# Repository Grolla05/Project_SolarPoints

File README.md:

# 💡 Project Solar Points — Smart Lighting for Low-Infrastructure Areas

> Light where there’s no infrastructure. Safety through simplicity and efficiency.

---

## 🌙 O que é o Solar Points?

O **Solar Points** é um sistema de iluminação pública autônomo e inteligente pensado para locais com pouca ou nenhuma infraestrutura elétrica, como:

- Paradas de ônibus
- Vielas e ruas estreitas
- Praças públicas
- Regiões periféricas e isoladas
- Áreas externas de residências

O objetivo permanece o mesmo: aumentar a segurança e o bem-estar comunitário com uma solução de baixo custo, sustentável e de fácil manutenção.

---

## 🔁 Evolução do projeto: de totalmente analógico para arquitetura digital

Inicialmente o projeto foi concebido como **100% analógico** (apenas componentes discretos e circuitos analógicos). Com as necessidades de sensoriamento mais preciso, flexibilidade operacional e otimização de consumo, o projeto evoluiu para uma **arquitetura digital/híbrida** baseada em microcontrolador e periféricos.

Essa mudança preserva os princípios de simplicidade, robustez e baixo consumo, ao mesmo tempo que agrega capacidades importantes:

- **Leitura digital de sensores** (intensidade de luz, distância/presença)
- **Decisões e temporizações programáveis** via firmware leve
- **Gerenciamento inteligente de energia** (controle de conversores DC-DC, modos de sono)
- **Comunicação entre módulos** via I2C/GPIO quando necessário

> A imagem anexada ao repositório ilustra o bloco funcional do novo design: microcontrolador central, sensores de luz e distância, gerenciamento de energia, baterias e conversores DC-DC.

---

## ⚙️ Principais funcionalidades (atualizado)

- **Ativação automática** baseada em sensores de luminosidade e presença
- **Modos ajustáveis** via firmware (p.ex. sensibilidades, temporização)
- **Operação autônoma** com painéis solares e baterias
- **Gestão adequada de energia** com conversores DC-DC e técnicas de baixo consumo
- **Projeto modular e replicável** com possibilidade de atualização de firmware

---

## 🛠️ Tecnologias e componentes (atualizado)

- **Microcontrolador** (unidade central de controle) — responsável por leitura de sensores e lógica de acionamento
- **Sensor de luminosidade** (LDR/photodiode + ADC) — medida de intensidade luminosa
- **Sensor de distância/presença** (ultrassom/IR) — detectar passagem ou presença
- **Conversores DC-DC** (step-up/step-down) — fornecimento estável para LEDs e eletrônica
- **Gestão de energia / Power Management** (monitoramento de bateria, carregamento solar)
- **Bateria recarregável e painéis solares**
- **LEDs de potência** para iluminação pública
- **Interfaces**: GPIOs para sinalização/controle, I2C para sensores/power ICs quando aplicável

---

## 🔍 Diagrama funcional

O diagrama no repositório mostra os blocos principais interconectados:

- 1 — Baterias (alimentação)
- 4 — Power Management (monitoramento/carregador)
- 11 — Conversão DC-DC (alimentação dos LEDs e eletrônica)
- 2 — Microcontrolador (núcleo lógico)
- 5 — Medição de intensidade luminosa (sensor)
- 6 — Sensor de distância/presença
- 3 — LED de status / power

O microcontrolador realiza a lógica central: lê sensores (GPIOs/ADC/I2C), decide quando ligar os LEDs e controla os conversores para otimizar consumo.

---

## ✨ Aplicações no mundo real

O Solar Points continua ideal para iluminar pontos sem infraestrutura elétrica: pontos de ônibus, caminhos em áreas rurais, entradas de condomínios e outras localidades onde uma solução autônoma e resiliente faz diferença.

---

## 👥 Autores

Desenvolvido por:

- **Felipe Grolla Freitas** – Engenharia de Controle e Automação (PUC-Campinas)
- **Guilherme Oliveira Nogueira** – Engenharia de Controle e Automação (PUC-Campinas)
- **Giovanna Lima Salvagnini** – Engenharia de Controle e Automação (PUC-Campinas)
- **Henrique Spadaccia Chambó** – Engenharia de Controle e Automação (PUC-Campinas)

---

> 🧠 "A simplicidade, aliada a decisões digitais pontuais, amplia o impacto das soluções de engenharia em contextos reais."

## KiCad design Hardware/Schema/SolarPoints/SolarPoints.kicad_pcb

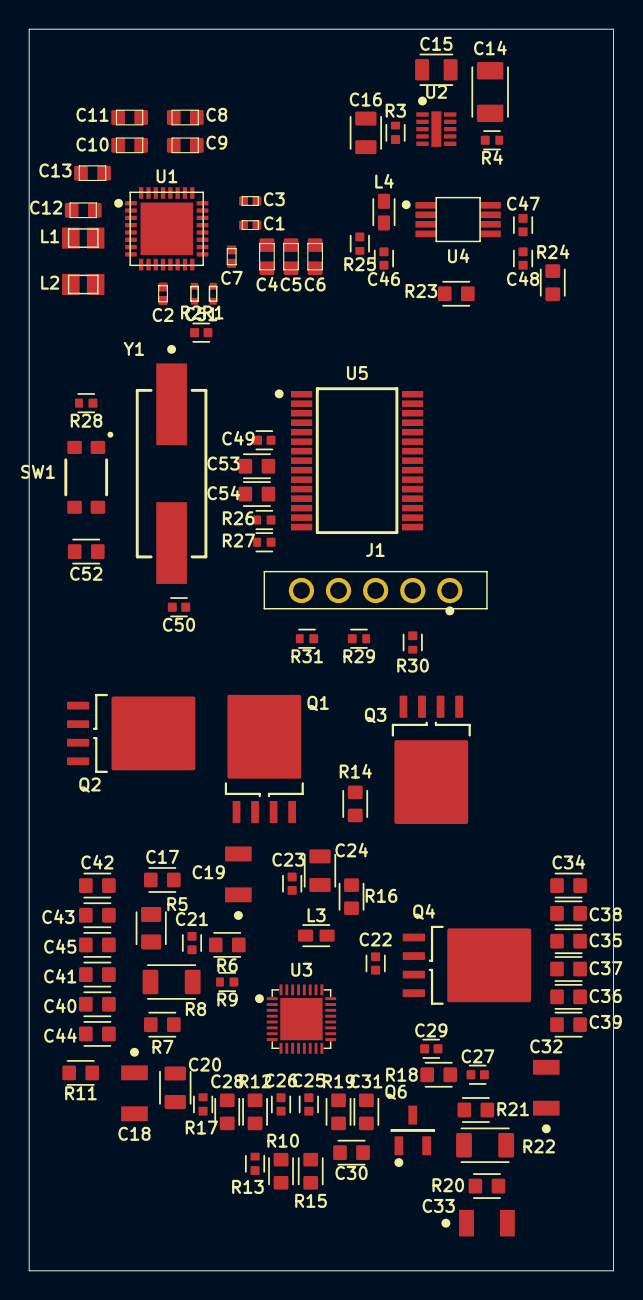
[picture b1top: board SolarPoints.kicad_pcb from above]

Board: 0 copper layers, 40.0 x 85.0 mm, 102 parts (0 on the bottom side), 63 nets, no tracks yet.

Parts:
C1, C3: 04023D105KAT2A
C2: KGM05CR71H104KH
C4, C5, C6, C8, C9, C10, C11, C12, C13: GRM188Z71A106KA73D
C7: GRM155Z71A225KE01D
C14: 12061C105K4Z4A
C15: 08051C104KAT2A
C16, C20: 08051C474K4Z2A
C17, C28: CL10A105KL8NNNC
C18, C19, C32, C33: C1206C153J5GACTU
C21: GRM155R71E103KA01D
C22, C23: GRM155R71H473KE14J
C24: C0805C225K5RACTU
C25, C26: CL05C101JB51PND
C27: CL05B681KB5VPNC
C29: CC0402JRNPO9BN150
C30: CL10C182JB8NNNC
C31: GRM1885C1H330JA01D
C34, C35, C36, C37, C38, C39, C40, C41, C42, C43, C44, C45: CL10A106MA8NRNC
C46, C48: GRM155R60J106ME15D
C47: GRM158R61A226ME15D
C49: CL05A105KO5NNNC
C50, C51: C0402C180J5GACTU
C52, C53, C54: 06035C104K4T2A
J1: 61300511021
L1, L2: MLZ2012M2R2HT000
L3, L4: LQM18PN2R2MFRL
Q1, Q2, Q3, Q4: SIJA72ADP-T1-GE3
Q6: SI2319DS-T1-E3
R1: ERJ2RKF4702X
R2: ERJ2RKF1503X
R3: ERJ2BSFR10X
R4: ERJ2RKF2001X
R5: CRCW08052R20FKEA
R6, R7, R16, R20, R21: RC0603FR-0710RL
R8, R22: ERJ8CWFR010V
R9: ERJ2GEJ1R0X
R10: ERJ3EKF3002V
R11: ERJ3EKF1003V
R12: RT0603FRE13330KL
R13, R17: ERJ2RKF2203X
R14: ERJ3GEYJ103V
R15: RT0603BRE0750RL
R18: ERJ3EKF1002V
R19: ERJS03F4022V
R23: ERJPA3F1003V
R24: ERJ3EKF7503V
R25: ERA2AED472X
R26, R27, R28: MCS0402MC1002FE000
R29, R30, R31: ERJ2RKF1001X
SW1: KMR221GLFS
U1: NPM1300-QEAA-R
U2: LTC2959IDDB#TRMPBF
U3: BQ25708RSNR
U4: PAM2401SCADJ
U5: R5F102AAASP#50
Y1: ABLS-20.000MHZ-B-2-T

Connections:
/GPIO4: R14.1, U1.11, U3.4
/sheet_1_Power Management/VBUSOUT: C3.1, U1.22
/sheet_2_Batteries/GPIO: R4.1, U2.8
/sheet_3_Battery Managemen.../ACN: C19.1, R6.1, U3.2
/sheet_3_Battery Managemen.../ACP: C18.1, R7.1, U3.3
/sheet_3_Battery Managemen.../BATDRV: Q6.1, U3.21
/sheet_3_Battery Managemen.../HIDRV1: Q1.4, U3.31
/sheet_3_Battery Managemen.../HIDRV2: Q4.4, U3.24
/sheet_3_Battery Managemen.../LODRV1: Q2.4, U3.29
/sheet_3_Battery Managemen.../LODRV2: Q3.4, U3.26
/sheet_3_Battery Managemen.../N$1_1: C28.1, R17.2, U3.6
/sheet_3_Battery Managemen.../PROCHOT: R15.2, U3.11
/sheet_3_Battery Managemen.../REGN: C24.1, R16.1, U3.28
/sheet_3_Battery Managemen.../SRN: C33.1, R20.1, U3.19
/sheet_3_Battery Managemen.../SRP: C32.1, R21.1, U3.20
/sheet_3_Battery Managemen.../SW1: C23.1, L3.1, Q1.1, Q1.2, Q1.3, Q2.5, U3.32
/sheet_3_Battery Managemen.../SW2: C22.2, L3.2, Q3.5, Q4.1, Q4.2, Q4.3, U3.23
/sheet_3_Battery Managemen.../VBUS: C20.1, R9.1, U3.1
/sheet_3_Battery Managemen.../VDDA: R12.2, R16.2, U3.7
/sheet_4_Switching DC-DC C.../EN: R25.1, U4.2
/sheet_5_Microcontroller/RESET: C52.1, J1.4, R28.1, R29.1, R31.1, SW1.1, SW1.4, U5.6
/sheet_5_Microcontroller/SCL: R26.1, U5.13
/sheet_5_Microcontroller/SDA: R27.1, U5.14
/sheet_5_Microcontroller/TOOL0: J1.2, R30.1, U5.5
GND: C1.2, C2.2, C3.2, C4.2, C5.2, C6.2, C7.2, C8.2, C9.2, C10.2, C11.2, C12.2, C13.2, C14.2, C15.2, C17.2, C18.2, C19.2, C20.2, C21.2, C24.2, C25.2, C26.2, C27.2, C28.2, C29.2, C30.2, C31.2, C32.2, C33.2, C34.2, C35.2, C36.2, C37.2, C38.2, C39.2, C40.2, C41.2, C42.2, C43.2, C44.2, C45.2, C46.2, C47.2, C49.1, C50.2, C51.2, C52.2, C53.2, C54.2, J1.1, Q2.1, Q2.2, Q2.3, Q3.1, Q3.2, Q3.3, R1.1, R2.1, R10.1, R11.1, R13.1, R17.1, R23.1, SW1.2, SW1.3, U1.2, U1.6, U1.33, U2.10, U2.11, U3.14, U3.27, U3.33, U4.4, U4.8, U5.11
unnamed: C17.1, R5.1
unnamed: C27.1, R18.1
unnamed: C30.1, R19.1
unnamed: J1.3, R29.2
unnamed: L4.2, U4.1
unnamed: C21.1, Q1.5, R6.2, R8.1, R9.2
unnamed: Q6.2, R21.2, R22.2
unnamed: L1.1, U1.3
unnamed: L2.1, U1.5
unnamed: R1.2, U1.17
unnamed: R2.2, U1.16
unnamed: C16.2, U2.4
unnamed: C16.1, U2.3
unnamed: C14.1, U2.9
unnamed: C23.2, U3.30
unnamed: C22.1, U3.25
unnamed: R12.1, R13.2, U3.18
unnamed: C31.1, R19.2, U3.16
unnamed: C29.1, R18.2, U3.17
unnamed: C26.1, R11.2, U3.8
unnamed: C25.1, U3.9
unnamed: R10.2, U3.10
unnamed: C48.2, R23.2, R24.1, U4.5
unnamed: C50.1, U5.9, Y1.2
unnamed: C51.1, U5.8, Y1.1
VBAT: C7.1, C47.1, C48.1, R24.2, U1.19, U4.7
VBAT_1: R3.1, R20.2, R22.1, U2.5
VBUS_1: C1.1, U1.21
VCC: C53.1, C54.1, J1.5, R26.2, R27.2, R28.2, R30.2, R31.2, U5.12
VCC_1: C15.1, R3.2, U2.1, U2.2
VIN: C40.1, C41.1, C42.1, C43.1, C44.1, C45.1, R5.2, R7.2, R8.2
VOUT1: C2.1, C12.1, L1.2, U1.1, U1.12
VOUT2: C13.1, L2.2, U1.32
VOUTLDO1: C8.1, C9.1, U1.29
VOUTLDO2: C10.1, C11.1, U1.31
VREG: C46.1, C49.2, L4.1, R25.2, U4.3, U5.10
VSYS: C34.1, C35.1, C36.1, C37.1, C38.1, C39.1, Q4.5, Q6.3, R4.2, U3.22
VSYS_1: C4.1, C5.1, C6.1, U1.4, U1.20, U1.28, U1.30

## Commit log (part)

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2025-05-10 Rename LINCENSE.txt to LICENSE.txt
2025-05-11 Update the finally circuit
2025-05-11 Rename image.png to First_version.png
2025-05-13 Rename image.png to BRD_circuit_image.png
2025-05-13 update files
2025-05-19 update test
2025-06-03 update feat
2025-06-14 Rename image.png to PCB.png
2025-06-14 Rename image.png to Schematics.png
2025-08-27 feat & style
2025-08-27 bug & docs
2025-08-28 feat
2025-09-04 docs
2025-09-08 style
2025-09-08 bug & perf
